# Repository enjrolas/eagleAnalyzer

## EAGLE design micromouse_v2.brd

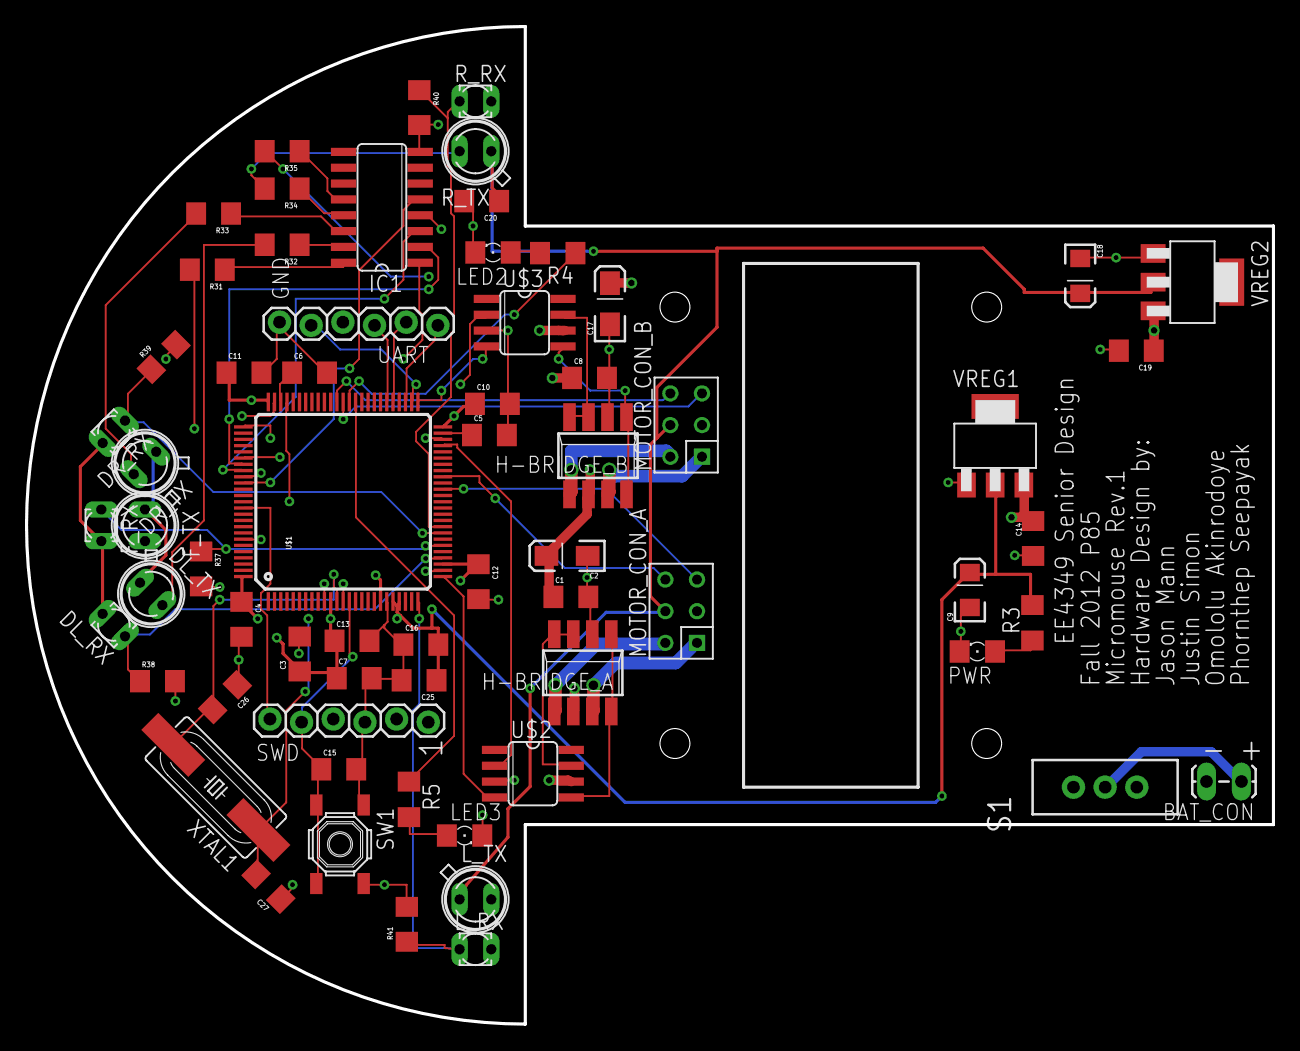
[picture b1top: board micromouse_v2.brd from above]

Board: 4 copper layers, 100.0 x 80.0 mm, 65 parts (0 on the bottom side), 59 nets.

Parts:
BAT_CON: 1X02_LOCK_LONGPADS
C1, C8: 0.1uF; 1206
C2, C17: 4.7uF; EIA3216-KIT
C3, C4, C7, C10, C11, C12, C14, C15, C19, C20: 0.1µF; 1206
C5, C6: 2.2µF; 1206
C9, C18: 10µF; EIA3216
C13: 4.7µF; 1206
C16: 10nF; 1206
C25: 1µF; 1206
C26, C27: 20pF; 1206
DL_RX: BPX81
DL_TX: SFH482
DR_RX: BPX81
DR_TX: SFH482
F_RX: BPX81
F_TX: SFH482
H-BRIDGE_A: ZXMHC3A01T8; SM8
H-BRIDGE_B: ZXMHC3A01T8; SM8
IC1: ULN2003AD; SO16
LED2, LED3: FKIT-LED-1206
L_RX: BPX81
L_TX: SFH482
MOTOR_CON_A: CON_HEADER_2X03-PTH; M2X3
MOTOR_CON_B: CON_HEADER_2X03-PTH; M2X3
PWR: FKIT-LED-1206
R3, R4, R5: 680; R1206
R31, R34, R35: 12; 1206
R32, R33: 5.6; 1206
R37, R38, R39, R40, R41: 1.8K; 1206
R_RX: BPX81
R_TX: SFH482
S1: SWITCH-SPDT
SW1: SW_TACT_SMALL
SWD: 1X06_LOCK
U$1: STM32F40X_QFP_PACKAGE; TQFP-100-14X14MM
U$2, U$3: MAX4427; SO08
UART: 1X06_LOCK
VREG1, VREG2: SOT-223
XTAL1: HC-49U

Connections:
3.3V: DL_RX.C, DR_RX.C, F_RX.C, L_RX.C, R_RX.C
3V3: C3.1, C4.1, C7.1, C9.A, C10.1, C11.1, C12.1, C13.1, C16.2, C25.1, R3.1, U$1.11, U$1.19, U$1.21, U$1.22, U$1.28, U$1.50, U$1.75, U$1.100, VREG1.2
5V: C18.A, C20.1, DL_TX.A, DR_TX.A, F_TX.A, L_TX.A, MOTOR_CON_A.4, MOTOR_CON_B.4, R_TX.A, UART.3, VREG2.2
DIR_A_H-BRIDGE: H-BRIDGE_A.1, H-BRIDGE_A.8, U$2.5
DIR_B_H-BRIDGE: H-BRIDGE_B.1, H-BRIDGE_B.8, U$3.5
DL_RX: DL_RX.E, R38.1, U$1.29
DL_TX: IC1.2, U$1.82
DR_RX: DR_RX.E, R39.1, U$1.33
DR_TX: IC1.3, U$1.83
F_RX: F_RX.E, R37.1, U$1.31
F_TX: IC1.1, U$1.81
GND: BAT_CON.2, C1.2, C2.C, C3.2, C4.2, C5.2, C6.2, C7.2, C8.2, C9.C, C10.2, C11.2, C12.2, C13.2, C14.2, C15.2, C16.1, C17.C, C18.C, C19.2, C20.2, C25.2, C26.1, C27.1, H-BRIDGE_A.2, H-BRIDGE_B.2, IC1.8, LED2.C, LED3.C, MOTOR_CON_A.3, MOTOR_CON_B.3, PWR.C, R37.2, R38.2, R39.2, R40.2, R41.2, SW1.1, SW1.2, SWD.3, U$1.10, U$1.20, U$1.27, U$1.74, U$1.94, U$2.3, U$3.3, UART.1, VREG1.1, VREG2.1
LED1: R4.1, U$1.62
LED2: R5.1, U$1.61
L_RX: L_RX.E, R41.1, U$1.25
L_TX: IC1.5, U$1.85
MOUT_A1: H-BRIDGE_A.5, MOTOR_CON_A.2
MOUT_A2: H-BRIDGE_A.7, MOTOR_CON_A.1
MOUT_B1: H-BRIDGE_B.5, MOTOR_CON_B.2
MOUT_B2: H-BRIDGE_B.7, MOTOR_CON_B.1
M_DIR_A: U$1.26, U$2.4
M_DIR_B: U$1.51, U$3.4
M_PWM_A: U$1.47, U$2.2
M_PWM_B: U$1.48, U$3.2
M_QE_AA: MOTOR_CON_A.5, U$1.40
M_QE_AB: MOTOR_CON_A.6, U$1.42
M_QE_BA: MOTOR_CON_B.5, U$1.63
M_QE_BB: MOTOR_CON_B.6, U$1.64
unnamed: IC1.16, R31.1
unnamed: C6.1, U$1.73
unnamed: C5.1, U$1.49
unnamed: PWR.A, R3.2
unnamed: C27.2, U$1.13, XTAL1.1
unnamed: LED2.A, R4.2
unnamed: LED3.A, R5.2
unnamed: IC1.15, R32.1
unnamed: IC1.14, R33.1
unnamed: IC1.13, R34.1
unnamed: IC1.12, R35.1
unnamed: F_TX.K, R31.2
unnamed: DL_TX.K, R32.2
unnamed: BAT_CON.1, S1.2
unnamed: R34.2, R_TX.K
unnamed: L_TX.K, R35.2
unnamed: DR_TX.K, R33.2
NRST: C15.1, SW1.3, SW1.4, SWD.5, U$1.14
PH0: C26.2, U$1.12, XTAL1.2
PWM_A_H-BRIDGE: H-BRIDGE_A.3, H-BRIDGE_A.4, U$2.7
PWM_B_H-BRIDGE: H-BRIDGE_B.3, H-BRIDGE_B.4, U$3.7
R_RX: R40.1, R_RX.E, U$1.34
R_TX: IC1.4, U$1.84
SWCLK: SWD.2, U$1.76
SWDIO: SWD.4, U$1.72
SWO: SWD.6, U$1.89
USART3_CTS: U$1.52, UART.2
USART3_RTS: U$1.53, UART.6
USART3_RX-I: U$1.56, UART.4
USART3_TX-O: U$1.55, UART.5
V_BATT: C1.1, C2.A, C8.1, C14.1, C17.A, C19.1, H-BRIDGE_A.6, H-BRIDGE_B.6, S1.1, U$2.6, U$3.6, VREG1.3, VREG2.3

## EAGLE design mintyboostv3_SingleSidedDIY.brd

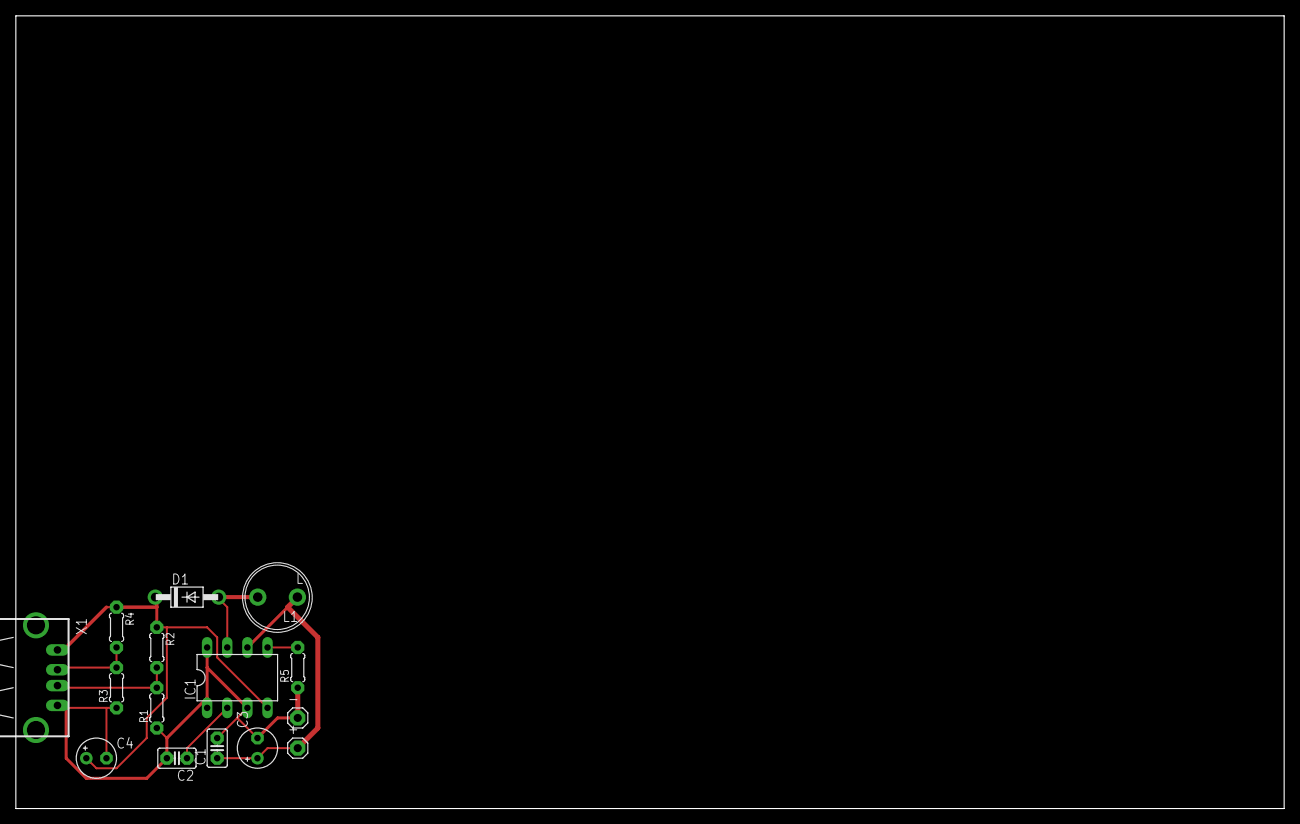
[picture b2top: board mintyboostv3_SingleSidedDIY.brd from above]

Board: 2 copper layers, 160.0 x 100.0 mm, 15 parts (0 on the bottom side), 8 nets.

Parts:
+: 1X01
-: 1X01
C1, C2: 0.1uF; C025-025X050
C3, C4: 220uF; E2,5-5
D1: 1N5817; DO41-7
IC1: LT1302; DIL08
L1: L; 6000
R1, R3: 49.9K; 0204/5
R2, R4: 75K; 0204/5
R5: 3.3k; 0204/5
X1: PN87520

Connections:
+5V: C4.+, D1.C, IC1.4, R2.1, R4.1, X1.1
BATT+: +.1, C1.1, C3.+, IC1.6, L1.1
D+: R1.2, R2.2, X1.3
D-: R3.2, R4.2, X1.2
GND: -.1, C1.2, C2.2, C3.-, C4.-, IC1.1, IC1.3, IC1.8, R1.1, R3.1, R5.1, X1.4
unnamed: C2.1, IC1.2
unnamed: IC1.5, R5.2
unnamed: D1.A, IC1.7, L1.2

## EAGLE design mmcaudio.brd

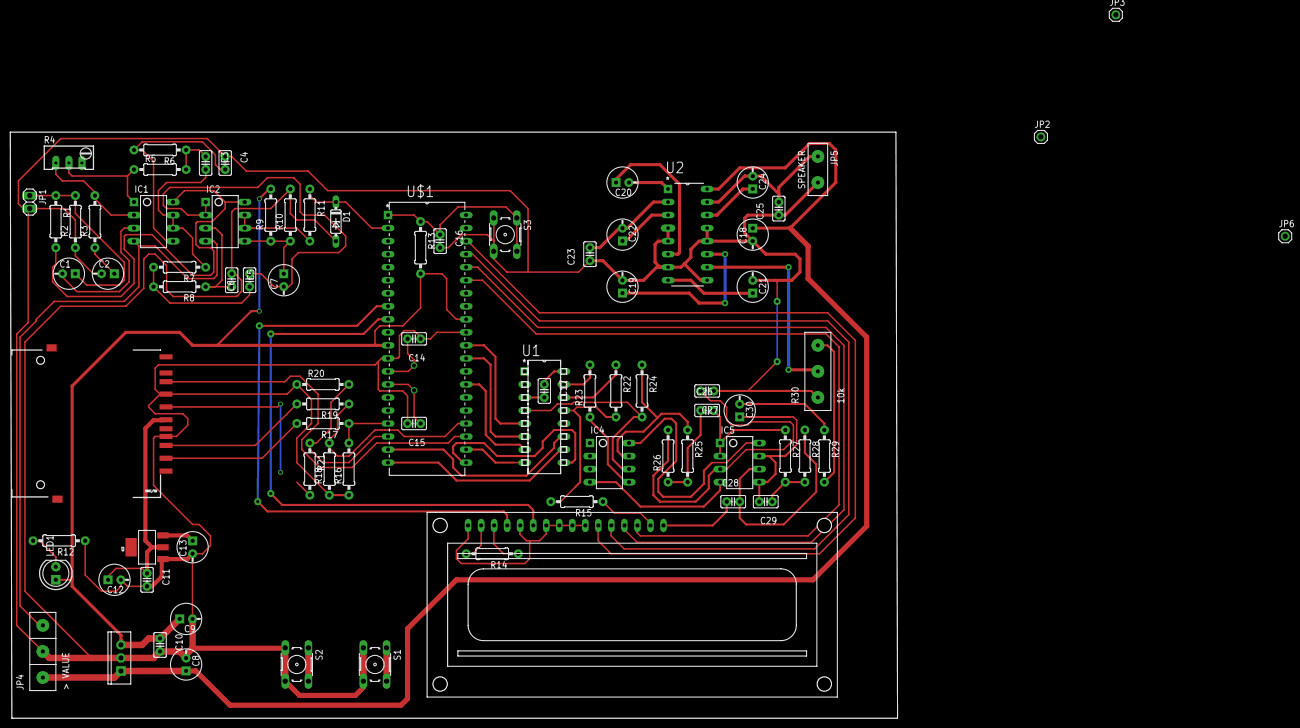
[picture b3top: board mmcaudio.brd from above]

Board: 2 copper layers, 173.0 x 114.3 mm, 83 parts (1 on the bottom side), 71 nets.

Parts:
C1, C7, C8, C9, C12, C13: 10uF; POL-CAP-COMMON
C2: 1uF; POL-CAP-COMMON
C3, C6, C26, C29: 223; C025-060X050
C4, C27, C28: 222; C025-060X050
C5: 103; C025-060X050
C10, C11, C16, C17, C23, C25: 104; C025-060X050
C14, C15: 22p; C025-060X050
C18, C19, C20, C21, C22, C24: 100uF; POL-CAP-COMMON
C30: POL-CAP-COMMON
D1: Z-5V1; DO35Z7
IC1, IC2, IC4, IC5: TL082; DIP08
IC3: LM1117; SOT223
JP1: 1X02
JP2, JP3, JP6: 1X01
JP4: 1X03/0.2"
JP5: SPEAKER; 1X02/0.5"
LED1: LED5MM
LM1: TO220-IGO
MMC/SD: SD_CARD_SOCKET4UCON; SDCARD_4UCONN
Q1: HC49/S
R1, R2, R9, R10, R13, R29: 10k; R-US-COMMON
R3, R11: 1k; R-US-COMMON
R4: 100k; RTRIM-COMMON
R5, R16, R17, R18, R19, R20, R21, R25: 6.8k; R-US-COMMON
R6, R26: 27k; R-US-COMMON
R7, R8: 3.3k; R-US-COMMON
R12: 330; R-US-COMMON
R14: 4k7; R-US-COMMON
R15: 100; R-US-COMMON
R22, R24: 2k2; R-US-COMMON
R23: 5k; R-US-COMMON
R27, R28: 1.5k; R-US-COMMON
R30: 10k; POT
S1, S2, S3: B3F-10XX
U1: DAC0808LCN; DIP254P762X508-16
U2: TEA2025B; DIP254P762X510-16
U$1: PIC18F4520-I/P; DIP254P1524X533-40
X1: HD44780LCD-1602; LCD1602

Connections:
+3V3: C11.1, C12.+, IC3.2, MMC/SD.4
+12V: C8.+, C18.+, IC1.8, IC2.8, IC4.4, IC5.4, JP4.1, LM1.IN, R1.2, U2.16
-12V: C17.2, IC1.4, IC2.4, IC4.8, IC5.8, JP4.3, U1.3
A1-MSB: U1.5, U$1.30
A2: U1.6, U$1.29
A3: U1.7, U$1.27
A4: U1.8, U$1.22
A5: U1.9, U$1.21
A6: U1.10, U$1.20
A7: U1.11, U$1.19
ADC: D1.C, JP3.1, R11.1, U$1.2
B1: S1.1, S1.2, U$1.33
B2: S2.1, S2.2, U$1.34
CLK: R20.2, R21.1, U$1.18
CONTR: R14.1, X1.3
CS: R16.2, R17.1, U$1.17
D4: U$1.38, X1.11
D5: U$1.37, X1.12
D6: U$1.36, X1.13
D7: U$1.35, X1.14
E: U$1.9, X1.6
GND: C2.-, C4.1, C5.1, C8.-, C9.-, C10.2, C11.2, C12.-, C13.-, C14.1, C15.2, C16.2, C18.-, C19.-, C21.-, C23.1, C25.1, C27.1, C28.1, D1.A, IC3.1, IC4.5, JP1.2, JP4.2, JP5.2, LM1.GND, MMC/SD.3, MMC/SD.6, R2.1, R10.2, R12.1, R16.1, R18.1, R20.1, R23.1, R30.3, S1.3, S1.4, S2.3, S2.4, S3.3, S3.4, U1.2, U2.4, U2.5, U2.7, U2.9, U2.12, U2.13, U$1.12, U$1.31, X1.16
IOUT: IC4.7, R24.1, R25.1
MISO: MMC/SD.7, U$1.23
MOSI: R18.2, R19.1, U$1.24
unnamed: C1.-, IC1.3
unnamed: IC1.2, R3.2, R4.1
unnamed: IC1.1, JP2.1, R4.2, R5.1
unnamed: C3.1, R5.2, R6.1
unnamed: C4.2, IC1.5, R6.2
unnamed: C3.2, IC1.6, IC1.7, R7.1
unnamed: C6.1, R7.2, R8.2
unnamed: C5.2, IC2.3, R8.1
unnamed: C6.2, C7.-, IC2.1, IC2.2
unnamed: C7.+, IC2.5, R9.1, R10.1
unnamed: IC2.6, IC2.7, R11.2
unnamed: C1.+, JP1.1, R1.1, R2.2
unnamed: C26.1, R25.2, R26.1
unnamed: C27.2, IC5.3, R26.2
unnamed: C26.2, IC5.1, IC5.2, R27.1
unnamed: C29.1, R27.2, R28.2
unnamed: C28.2, IC5.6, R28.1
unnamed: C29.2, C30.+, IC5.5, IC5.7
unnamed: C30.-, JP6.1, R29.1
unnamed: C19.+, U2.11
unnamed: C20.+, U2.6
unnamed: C20.-, U2.1
unnamed: C24.-, C25.2, JP5.1, U2.15
unnamed: C24.+, U2.14
unnamed: C22.-, C23.2, U2.2
unnamed: C22.+, U2.3
unnamed: C21.+, U2.8
unnamed: R29.2, R30.1
unnamed: C2.+, R3.1
unnamed: R15.1, X1.15
unnamed: C17.1, U1.16
unnamed: IC4.6, R24.2, U1.4
unnamed: MMC/SD.1, R17.2
unnamed: LED1.K, R12.2
unnamed: MMC/SD.2, R19.2
unnamed: MMC/SD.5, R21.2
OSC1: C14.2, Q1.1, U$1.13
OSC2: C15.1, Q1.2, U$1.14
PWR_AMP: R30.2, U2.10
RESET: C16.1, R13.1, S3.1, S3.2, U$1.1
RS: U$1.8, X1.4
VCC: C9.+, C10.1, C13.+, IC3.3, LED1.A, LM1.OUT, R9.2, R13.2, R15.2, R22.2, U1.13, U$1.11, U$1.32
VDD: R14.2, X1.2
VREF+: R22.1, U1.14
VREF-: R23.2, U1.15
VSS: X1.1, X1.5, X1.7, X1.8, X1.9, X1.10

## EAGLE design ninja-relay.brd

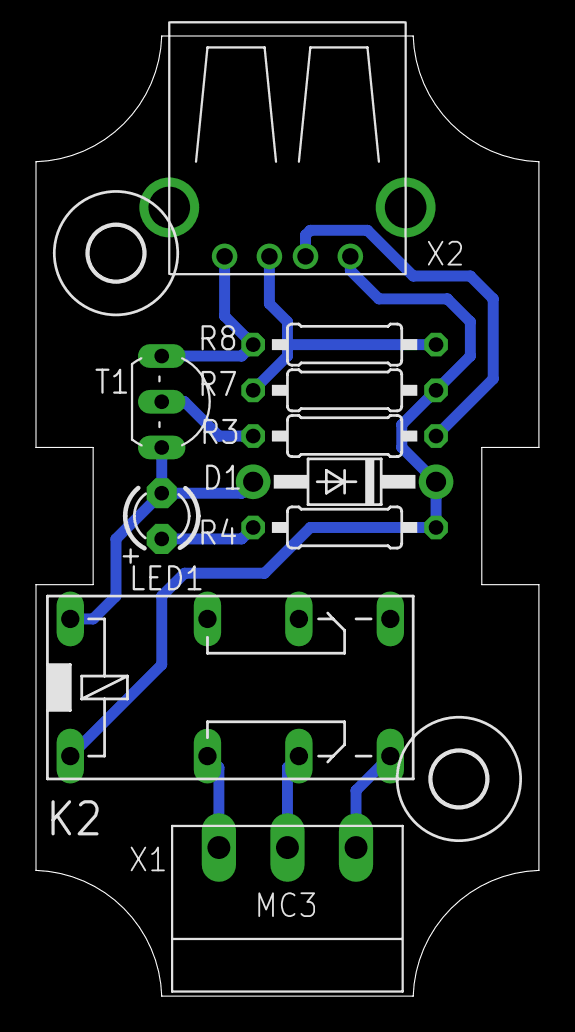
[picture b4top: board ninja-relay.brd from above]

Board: 2 copper layers, 27.9 x 53.3 mm, 12 parts (0 on the bottom side), 10 nets.

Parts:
D1: 1N4004; DO41-10
H1, H2: MOUNT-HOLE3.0; 3,0
K2: 351
LED1: LED3MM
R3: 1K; 0207/10
R4: 470R; 0207/10
R7: 10K; 0207/10
R8: 18K; 0207/10
T1: 2N2222; TO92-EBC-OVAL
X1: MC3
X2: USB-A-H

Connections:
GND: R8.2, T1.E, X2.GND
unnamed: K2.O1, X1.2
unnamed: K2.P1, X1.1
unnamed: K2.S1, X1.3
unnamed: D1.A, K2.16, LED1.K, T1.C
unnamed: D1.C, K2.1, R4.1, R7.1, X2.VBUS
unnamed: R3.1, T1.B
unnamed: R3.2, X2.D-
unnamed: LED1.A, R4.2
unnamed: R7.2, R8.1, X2.D+

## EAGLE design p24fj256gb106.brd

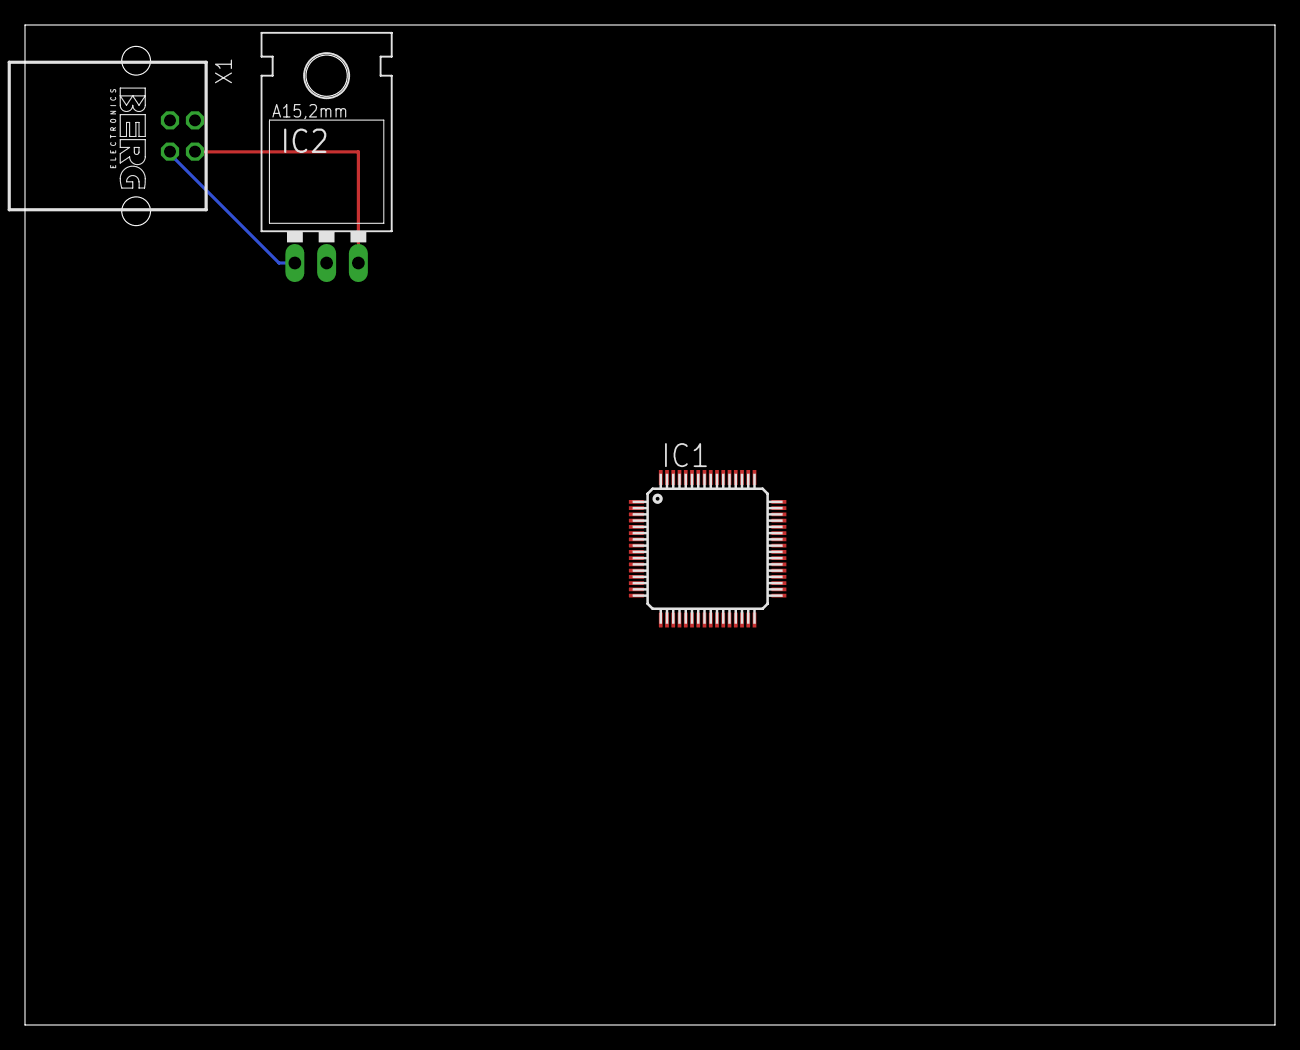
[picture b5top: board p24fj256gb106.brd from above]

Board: 2 copper layers, 100.0 x 80.0 mm, 3 parts (0 on the bottom side), 4 nets.

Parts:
IC1: PIC24FJ256GB106; TQFP64-10X10
IC2: LM317MABT; TO220L1
X1: PN61729

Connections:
GND: IC2.1, X1.4
unnamed: IC2.3, X1.1
VDD: IC1.10, IC1.26, IC1.38
VSS: IC1.9, IC1.25, IC1.41

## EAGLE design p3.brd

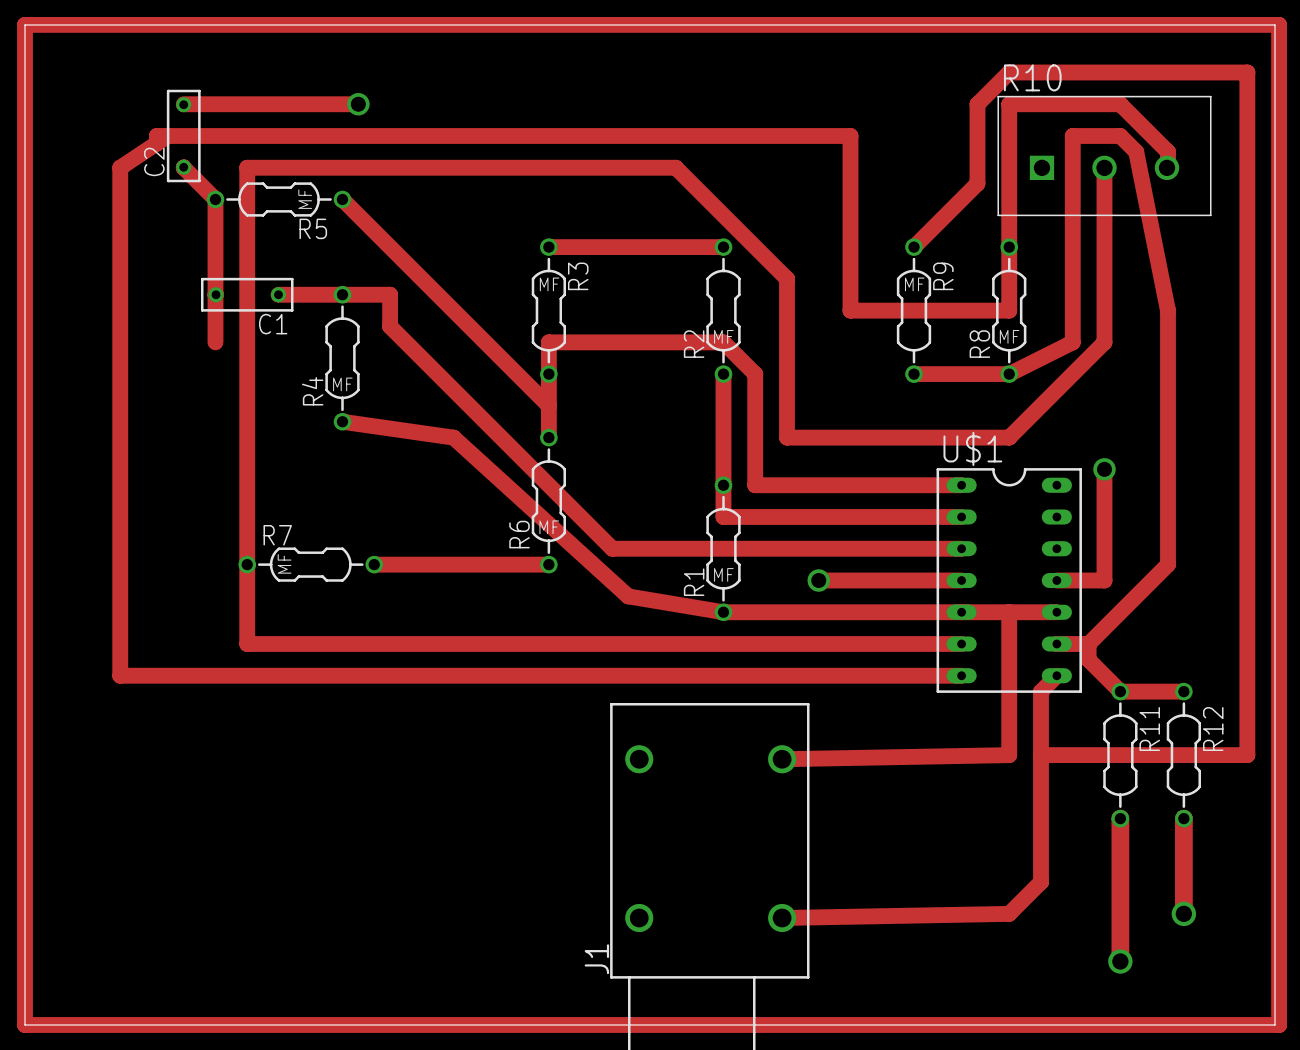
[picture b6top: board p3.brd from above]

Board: 2 copper layers, 100.0 x 80.0 mm, 16 parts (0 on the bottom side), 11 nets.

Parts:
C1, C2: 10n; BOX-2.5MM-7.2MM
J1: MONOSW1GND; NEUTRIK-NRJ4HM-1
R1, R7: 100k; 0.25W-0.4IN-METALFILM
R2: 56k; 0.25W-0.4IN-METALFILM
R3: 2.2k; 0.25W-0.4IN-METALFILM
R4, R5: 5.6k; 0.25W-0.4IN-METALFILM
R6: 100; 0.25W-0.4IN-METALFILM
R8, R9: 1k; 0.25W-0.4IN-METALFILM
R10: 100k; POT-SIDE-16MM-BITECH-P160KN
R11, R12: 1k; 0.25W-0.4IN
U$1: OPAMP-QUADTL074; DIP14

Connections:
0: J1.T, R1.1, R4.1, U$1.5, U$1.10
unnamed: R1.2, R2.1, U$1.2
unnamed: R2.2, R3.1
unnamed: R3.2, R5.1, R6.2, U$1.1
unnamed: R6.1, R7.2
unnamed: R7.1, R10.P$2, U$1.6
unnamed: R8.2, R10.P$3, U$1.7
unnamed: R8.1, R9.2, R11.1, R12.1, U$1.9
unnamed: J1.S, R9.1, U$1.8
unnamed: C1.P$1, R4.2, U$1.3
unnamed: C1.P$2, C2.P$1, R5.2

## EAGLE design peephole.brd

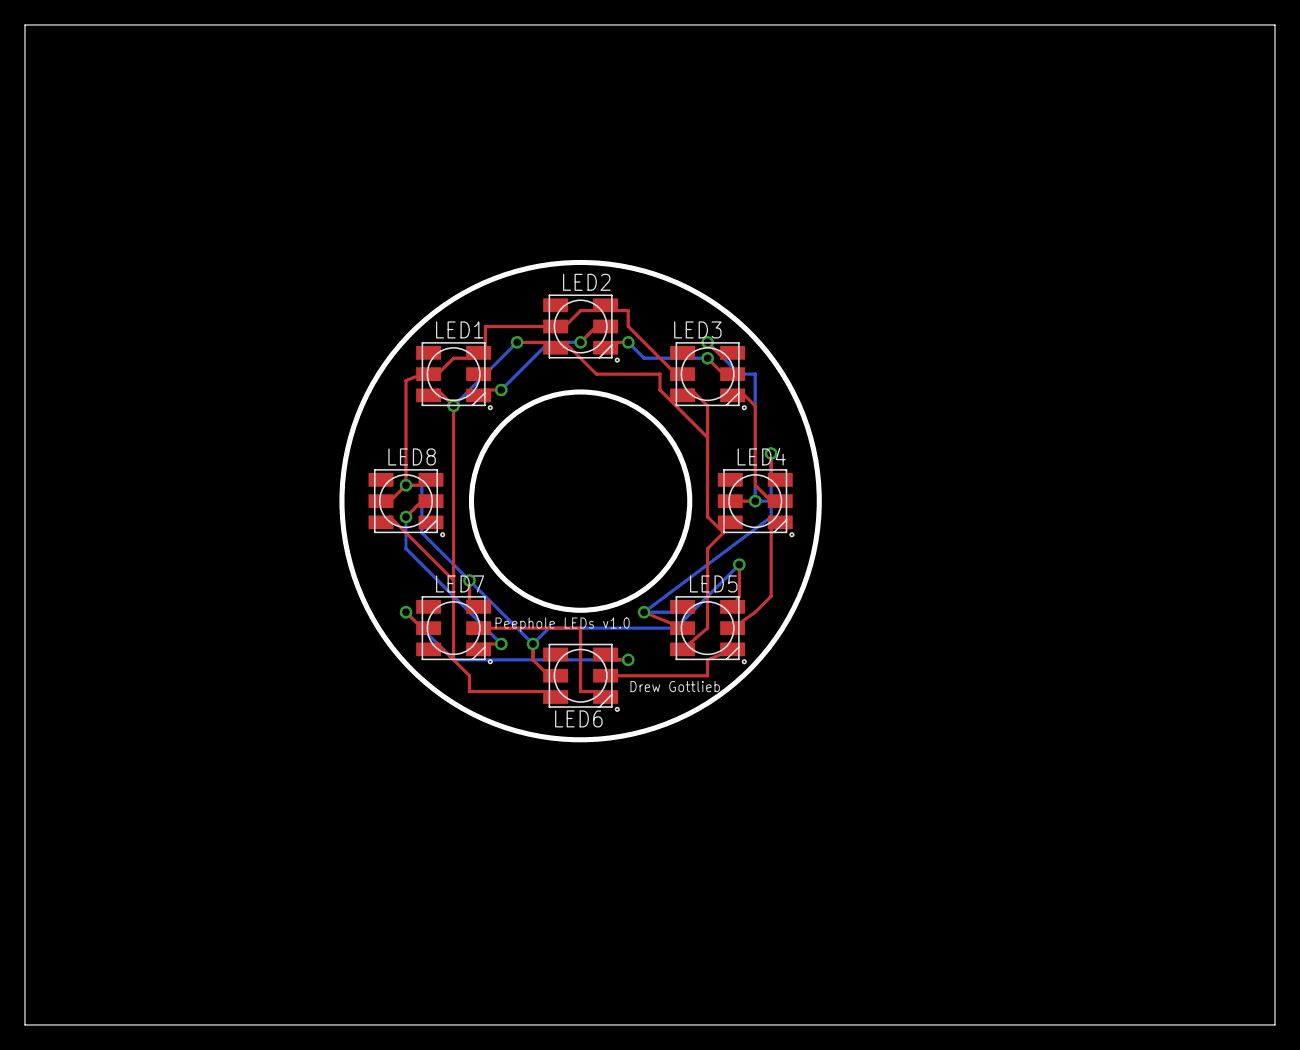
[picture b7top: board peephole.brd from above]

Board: 2 copper layers, 100.0 x 80.0 mm, 8 parts (0 on the bottom side), 9 nets.

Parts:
LED1, LED2, LED3, LED4, LED5, LED6, LED7, LED8: WS2812

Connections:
GND: LED1.VSS, LED2.VSS, LED3.VSS, LED4.VSS, LED5.VSS, LED6.VSS, LED7.VSS, LED8.VSS
unnamed: LED5.DO, LED6.DI
unnamed: LED6.DO, LED7.DI
unnamed: LED7.DO, LED8.DI
unnamed: LED4.DO, LED5.DI
unnamed: LED3.DO, LED4.DI
unnamed: LED2.DO, LED3.DI
unnamed: LED1.DO, LED2.DI
VDD: LED1.LEDVDD, LED1.VDD, LED2.LEDVDD, LED2.VDD, LED3.LEDVDD, LED3.VDD, LED4.LEDVDD, LED4.VDD, LED5.LEDVDD, LED5.VDD, LED6.LEDVDD, LED6.VDD, LED7.LEDVDD, LED7.VDD, LED8.LEDVDD, LED8.VDD

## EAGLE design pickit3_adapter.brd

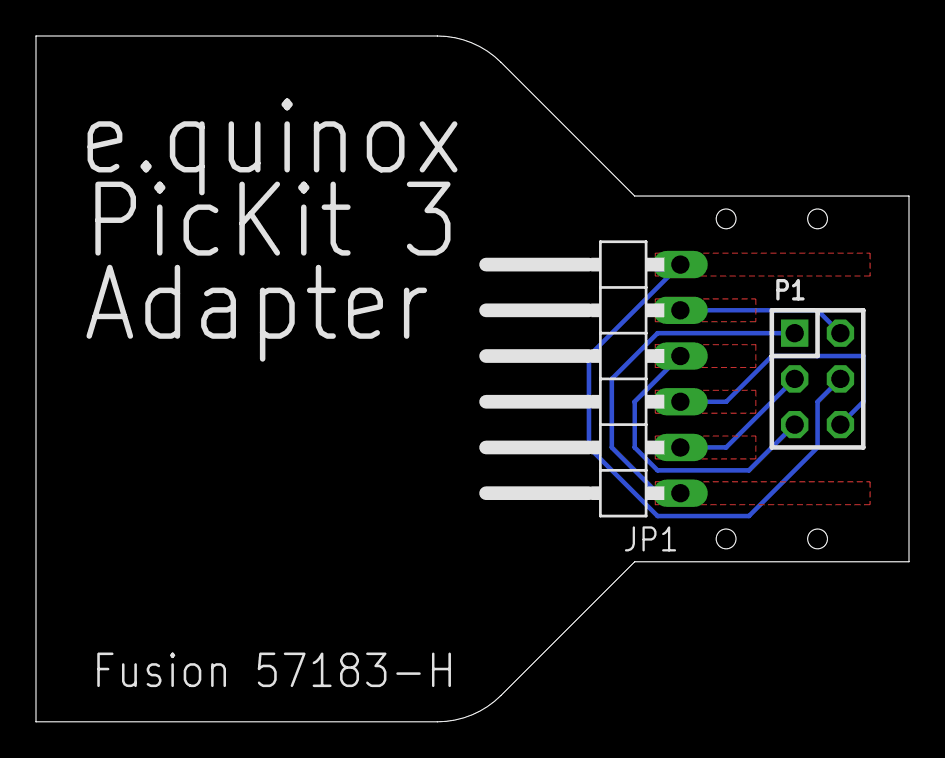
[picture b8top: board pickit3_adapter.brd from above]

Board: 2 copper layers, 48.5 x 38.1 mm, 3 parts (1 on the bottom side), 6 nets.

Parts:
JP1: 1X06/90
P1: ICSP; DIL-100-2X03
U$1: EQNXLOGO

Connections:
0V: JP1.3, P1.6
!MCLR!: JP1.1, P1.1
+3V3: JP1.2, P1.3
PGC: JP1.5, P1.2
PGD: JP1.4, P1.5
PGM: JP1.6, P1.4

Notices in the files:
parts and their libraries:
SparkFun-Connectors: Licensing: CC v3.0 Share-Alike You are welcome to use this library for commercial purposes.
